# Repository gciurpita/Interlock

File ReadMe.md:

### RR Interlock - Bill Lupoli's New Haven

Arduino interlock route controller,
aligns multiple turnouts through interlock
by pressing buttons at either end of route.

Controller uses hardware shown at right.
~12V input top left to ~6V down converter to Arduino UNO board bottom left.
Three custom Tortoise Driver and I/O PCBs
using MCP23017 I2C I/O expander
to control up to 8 tortoise switch machines using LM324 op-amps and
eight GPIOs.

<!-- -----------------------------------------------  ---------------------- -->
<h4> PCB Wire Connections </h4>

<table border=1 cellspacing=0 align=right>
 <tr> <th colspan=2> PCB 4
 <tr> <th> Sw <th> But
 <tr> <td align=center> &nbsp; <td align=center>  &nbsp;
 <tr> <td align=center> &nbsp; <td align=center>  &nbsp;
 <tr> <td align=center> &nbsp; <td align=center>  &nbsp;
 <tr> <td align=center> &nbsp; <td align=center>  &nbsp;

 <tr> <td align=center> &nbsp; <td align=center>  &nbsp;
 <tr> <td align=center> &nbsp; <td align=center>  &nbsp;
 <tr> <td align=center> &nbsp; <td align=center>  &nbsp;
 <tr> <td align=center> &nbsp; <td align=center>  &nbsp;
</table>

<table border=1 cellspacing=0 align=right>
 <tr> <th colspan=2> PCB 3
 <tr> <th> Sw <th> But
 <tr> <td align=center>  69 <td align=center>  A1
 <tr> <td align=center>  70 <td align=center>  A2
 <tr> <td align=center>  71 <td align=center>  A3
 <tr> <td align=center>  72 <td align=center>  A4
 <tr> <td align=center> &nbsp; <td align=center> B1
 <tr> <td align=center> &nbsp; <td align=center> B2
 <tr> <td align=center> &nbsp; <td align=center> B3
 <tr> <td align=center> &nbsp; <td align=center> B4
</table>

<table border=1 cellspacing=0 align=right>
 <tr> <th colspan=2> PCB 2
 <tr> <th> Sw <th> But
 <tr> <td align=center>  59 <td align=center>  C1
 <tr> <td align=center>  61 <td align=center>  C2
 <tr> <td align=center>  63 <td align=center>  C3
 <tr> <td align=center>  64 <td align=center>  C4
 <tr> <td align=center>  65 <td align=center>  C5
 <tr> <td align=center>  66 <td align=center>  C6
 <tr> <td align=center>  67 <td align=center>  C7
 <tr> <td align=center>  68 <td align=center>  C8
</table>

<table border=1 cellspacing=0 align=right>
 <tr> <th colspan=2> PCB 1
 <tr> <th> Sw <th> But
 <tr> <td align=center>  51 <td align=center>  X1
 <tr> <td align=center>  52 <td align=center>  X2
 <tr> <td align=center>  53 <td align=center>  X3
 <tr> <td align=center>  54 <td align=center>  &nbsp;

 <tr> <td align=center>  55 <td align=center>  &nbsp;
 <tr> <td align=center>  56 <td align=center>  &nbsp;
 <tr> <td align=center>  57 <td align=center>  &nbsp;
 <tr> <td align=center>  58 <td align=center>  &nbsp;
</table>

<!-- -----------------------------------------------  ---------------------- -->
<h4> Panel Description  </h4>

<i>westIntLck.cpp</i> contains tables describing the panel:
buttons, turnouts and routes.
This description requires a minimal understanding of programming
to make modifications.

<p>
Descriptions of both buttons and turnouts
includes identifying the corresponding
chip and port bit along with a label.

<p>
Buttons are described in <i>butIos []</i>.
<i>Ba1</i> is a numeric symbol uniquely identifying each button,
the <i>B</i> prefix identifies it as a button and
<i>a1</i> corresponds to the label on the panel.
The <i>0, 0, "A1"</i> identifies the input on
chip 0, port bit 0 (the first or least significant bit) and
a text string label, <i>A1</i>.
There are at most 8 bits on each chip,
some spare bits are available.

<blockquote><pre>
const PROGMEM ButIo_t butIos [] = {
    { Ba1, { 0, 0, "A1" }},
    ...
    { Bc6, { 1, 5, "C6" }},
    ...
    { Bc9, { 2, 0, "C9" }},
    { Bx1, { 2, 1, "X1" }},
    { Bx2, { 2, 2, "X2" }},
    ...
    { B_0, { 0, 0, ""   }},
};
</blockquote></pre>

There is an entry for each switch machine position.
<i>s02r</i> is the variable name of the entry used in the <i>routes</i> table.
The first three fields, <i>2, R, 1</i>,
include a numeric value for the switch machine,
a symbol, <i>N/R</i> identifying the position as normal/reverse and
the bit value, 0/1 for that position.
The last three fields,
<i>0, 1, "s02r"</i>, like the button entry
specify the chip, port bit and label.

<blockquote><pre>
// machine address and polarity
const PROGMEM SwMach_t s02n = {  2, N, 0, { 0, 1, "s02n" }};
const PROGMEM SwMach_t s02r = {  2, R, 1, { 0, 1, "s02r" }};

const PROGMEM SwMach_t s14n = { 14, N, 0, { 1, 5, "s14n" }};
const PROGMEM SwMach_t s14r = { 14, R, 1, { 1, 5, "s14r" }};

const PROGMEM SwMach_t s21n = { 21, N, 0, { 2, 4, "s21n" }};
const PROGMEM SwMach_t s21r = { 21, R, 1, { 2, 4, "s21r" }};
</blockquote></pre>

Routes are described in the routes table, <i>routes []</i>.
Each entry specifies a pair a buttons and
one or more switch machine position references (i.e. pointers).

<blockquote><pre>
const PROGMEM Route_t routes [] = {
    { Ba1, Bc1, { &s21r, &s19n, &s15r, &s14n, &s06n }},
    { Ba1, Bc2, { &s21r, &s19n, &s15n, &s10n, &s06n }},
    ...
    { Ba4, Bc4, { &s20n, &s16n, &s17n, &s11n, &s12n, &s07n, &s02r, &s01n }},
    ...
}
</blockquote></pre>

Some routes are ambiguous,
a pair of buttons can select more than one route.
<blockquote><pre>
    { Ba4, Bc3, { &s20n, &s16n, &s17n, &s11n, &s12n, &s07n, &s02r, &s01r }},
    { Ba4, Bc3, { &s20r, &s16n, &s17n, &s11n, &s12n, &s07n, &s02r, &s01r }},
</blockquote>

The code repeatedly
* monitors the button input ports
* detects that two or more buttons have been pressed
* uses <i>butIos []</i> to match the chip and port bit to button IDs
* searches the routes table for an entry with that pair of buttons, and
* sets the corresponding bits to position the switch
for each machine in the route.

<!-- -----------------------------------------------  ---------------------- -->
<hr>
<h4> Code Description </h4>

<b>setup ()</b> 
sets the serial monitor bit rate,
configures pins 5-13 as outputs,
initializes the I2C interface (i.e. <i>Wire</i>) and
calls <i>i2cCfg ()</i> to configure the
I/O expanders on each switch machine driver board.

<p>
<b>loop ()</b> invokes
<ul>
 <li> <i>ledStrobe ()</i>
 <li> <i>butScan ()</i>
 <li> <i>pcRead ()</i>
 <li> <i>tglTest ()</i>
</ul>

<p>
<b>ledStrobe (void)</b>
flashes/winks an LED at one of three different sequences,
on/off periods.

<p>
<b>butScan (void)</b>
reads GPIO-B, the button input port of each chip,
checks for a change in state,
waits WAIT_CNT iterations to debounce
before recognizing that one or more buttons have been pressed and 
calling <i>mapButtons ()</i> 

<p>
<b>mapButtons ()</b>
translates the chip and port bit of the button
into a button ID (e.g. <i>Ba1</i>) using <i>butFind ()</i>,
appending the button ID to <i>list []</i> 
<i>chkRoutes ()</i> is invoked
if two or more buttons are pressed.
<i>tglTestEn</i> is toggled
if the three: <i>Ba1, Ba3</i> and <i>Ba0</i> are pressed.

<p>
<b>butFind ()</b>
searches <i>butIos []</i> for
entries matching the chip and port bit arguments.
The following <i>butIos []</i> entry
specifies a button-ID, chip, port-bit and label
<blockquote>
    { Ba1, { 0, 0, "A1" }},
</blockquote>

<p>
<b>int chkRoutes ()</b> 
searches for a route entry with matching buttons.
The following <i>routes []</i> entry
specifies two buttons followed by one or more 
pointers (e.g. <i>&amp;s21n</i> to <i>SwMach_t</i>)
<blockquote>
    { Ba1, Bc1, { &s21r, &s19n, &s15r, &s14n, &s06n }},
</blockquote>
<i>chkButtons ()</i> is used to compare the button entries from a route
to the buttons in <i>list []</i> from <i>mapButtons ()</i>.

<p>
A <i>SwMach_t</i> entry specifies
a switch machine ID, position (i.e. N/R),
bit value for that position and <i>I2cBitDef_t</i> 
which specified a chip, port bit and label
<blockquote>
const PROGMEM SwMach_t s21r = { 21, R, 1, { 2, 4, "s21r" }};
</blockquote>

<p>
<b>int chkButtons ()</b>
compares each of three possible button arguments
to each entry in <i>list []</i>.

<p>
<b>void bitUpdate ()</b> 
updates a specific port bit on a specified chip
by reading and masking the port value 
to only update the state (0, 1) of the specified bit.

<p>
<b>i2cCfg () </b> 
configures GPIO-A and B direction registers
for output and input respectively.
It enables the pull-up resistors on GPIO-B.
set GPIO-B

<p>
<b>i2cWrite (int chip, int port, byte val) </b> 
writes the 8-bit value to the specific chip and port.
After writing the direction registers
it attempts to read them back and
discontinue the loop assuming not chip exists at that bus address.

<p>
<b>i2cWrite (int chip, int port, byte val) </b> 
writes the 8-bit value to the specific chip and port.

<p>
<b>test ()</b>
sequentially sets each port bit for 500 msec
first for GPIO-A and then GPIO-B (should have no effect).

<p>
<b>tglTest (void)</b>,
when enabled,
toggles all 8-its of GPIO-A on each chip every 4 seconds.
It first tests if <i>tglTestEn</i> is set.
It then tests if the time has expired.
It then inverts <i>tglTestState</i> and
writes it to GPIO-A of each chip.

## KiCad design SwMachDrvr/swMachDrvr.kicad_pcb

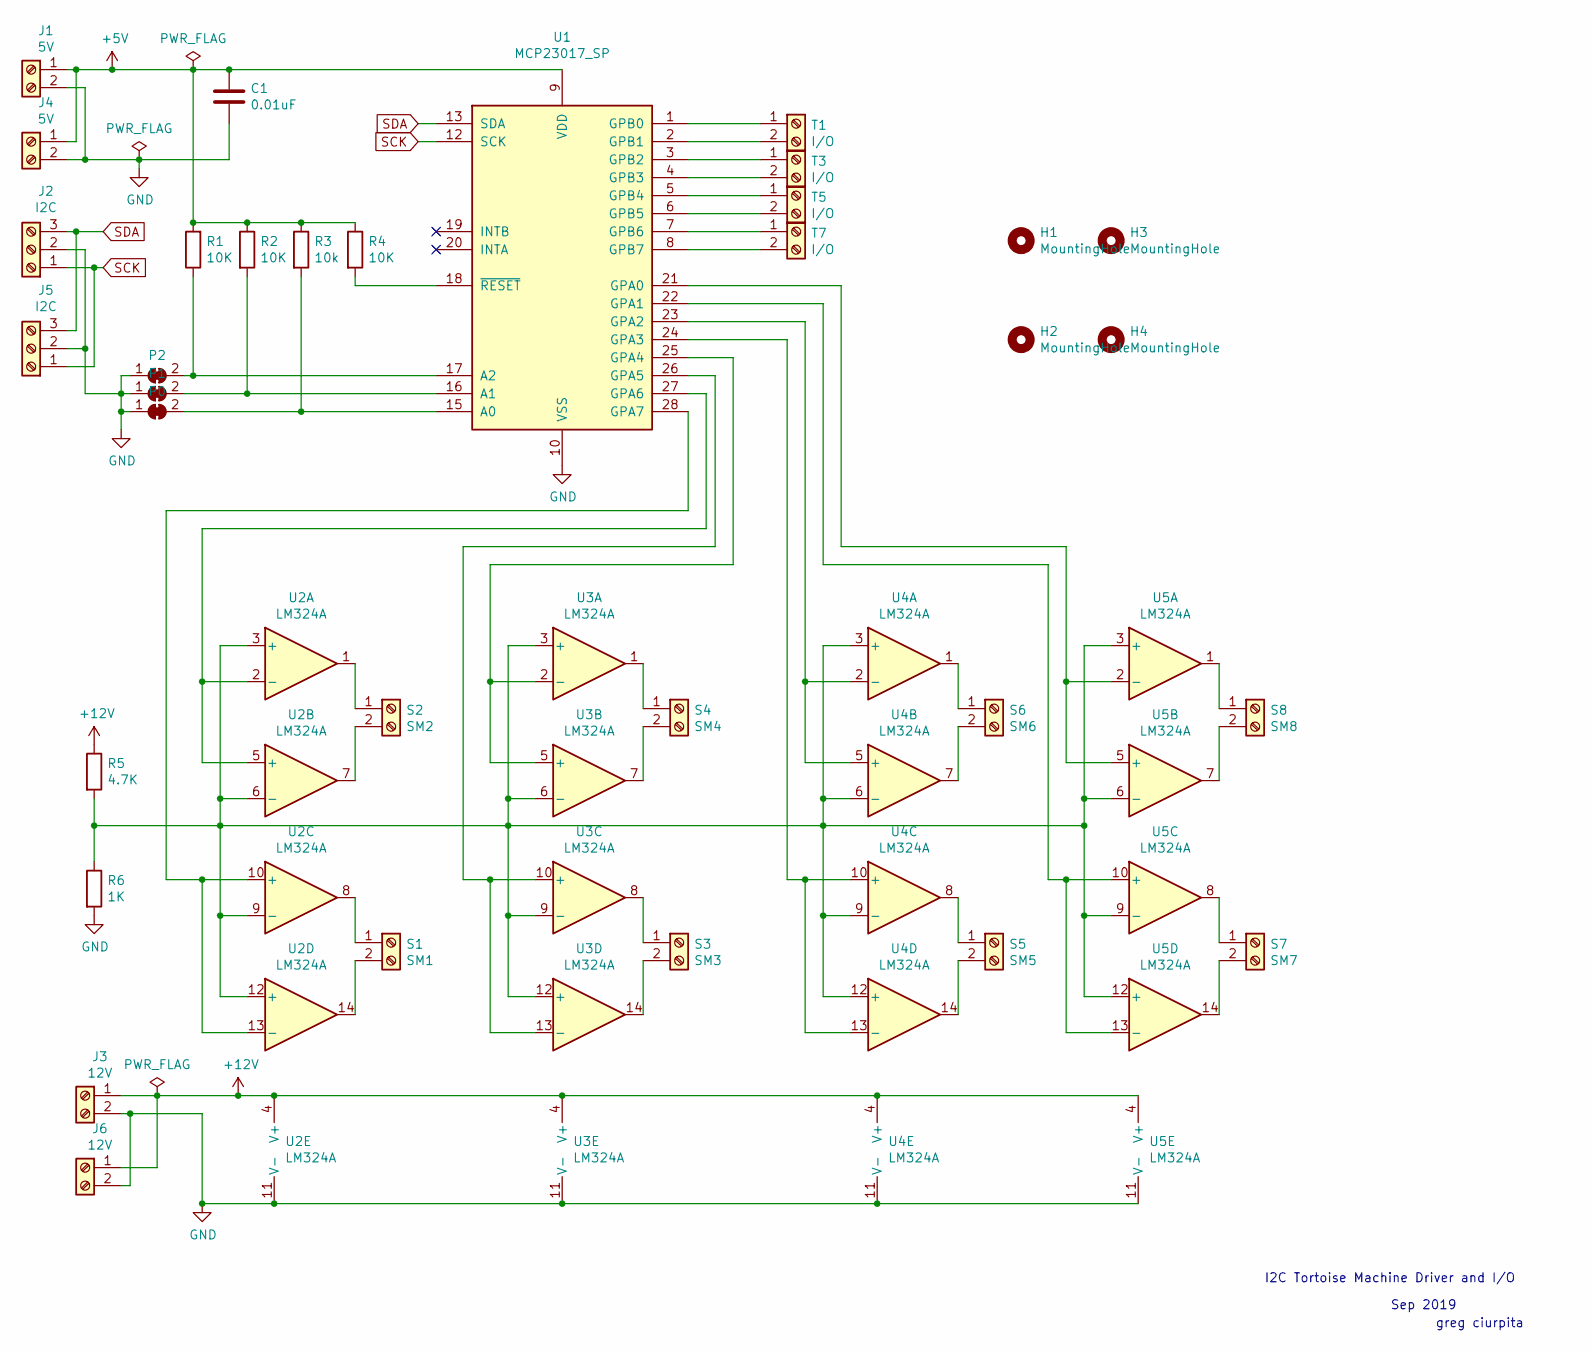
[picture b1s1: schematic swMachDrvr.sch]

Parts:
C1: 0.01uF; C_Disc_D4.3mm_W1.9mm_P5.00mm
H1, H2, H3, H4: MountingHole; MountingHole_3.5mm
J1, J4: 5V; PinHeader_1x02_P2.54mm_Vertical
J2, J5: I2C; PinHeader_1x03_P2.54mm_Vertical
J3, J6: 12V; PinHeader_1x02_P2.54mm_Vertical
P0, P1, P2: br; SolderJumper-2_P1.3mm_Bridged_RoundedPad1.0x1.5mm
R1, R2, R4: 10K; R_Axial_DIN0207_L6.3mm_D2.5mm_P7.62mm_Horizontal
R3: 10k; R_Axial_DIN0207_L6.3mm_D2.5mm_P7.62mm_Horizontal
R5: 4.7K; R_Axial_DIN0207_L6.3mm_D2.5mm_P7.62mm_Horizontal
R6: 1K; R_Axial_DIN0207_L6.3mm_D2.5mm_P7.62mm_Horizontal
S1: SM1; PinHeader_1x02_P2.54mm_Vertical
S2: SM2; PinHeader_1x02_P2.54mm_Vertical
S3: SM3; PinHeader_1x02_P2.54mm_Vertical
S4: SM4; PinHeader_1x02_P2.54mm_Vertical
S5: SM5; PinHeader_1x02_P2.54mm_Vertical
S6: SM6; PinHeader_1x02_P2.54mm_Vertical
S7: SM7; PinHeader_1x02_P2.54mm_Vertical
S8: SM8; PinHeader_1x02_P2.54mm_Vertical
T1, T3, T5, T7: I/O; PinHeader_1x02_P2.54mm_Vertical
U1: MCP23017_SP; DIP-28_W7.62mm_Socket
U2, U3, U4, U5: LM324A; DIP-14_W7.62mm_Socket

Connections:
+5V: C1.1, J1.1, J4.1, R1.2, R2.1, R3.1, R4.1, U1.9 (VDD)
+12V: J3.1, J6.1, R5.1, U2.4 (V+), U3.4 (V+), U4.4 (V+), U5.4 (V+)
GND: C1.2, J1.2, J2.2, J3.2, J4.2, J5.2, J6.2, P0.1 (A), P1.1 (A), P2.1 (A), R6.2, U1.10 (VSS), U2.11 (V-), U3.11 (V-), U4.11 (V-), U5.11 (V-)
unnamed: P0.2 (B), R3.2, U1.15 (A0)
unnamed: P1.2 (B), R2.2, U1.16 (A1)
unnamed: P2.2 (B), R1.1, U1.17 (A2)
unnamed: R4.2, U1.18 (~RESET~)
unnamed: R5.2, R6.1, U2.3 (+), U2.6 (-), U2.9 (-), U2.12 (+), U3.3 (+), U3.6 (-), U3.9 (-), U3.12 (+), U4.3 (+), U4.6 (-), U4.9 (-), U4.12 (+), U5.3 (+), U5.6 (-), U5.9 (-), U5.12 (+)
unnamed: S1.1, U2.8
unnamed: S1.2, U2.14
unnamed: S2.1, U2.1
unnamed: S2.2, U2.7
unnamed: S3.1, U3.8
unnamed: S3.2, U3.14
unnamed: S4.1, U3.1
unnamed: S4.2, U3.7
unnamed: S5.1, U4.8
unnamed: S5.2, U4.14
unnamed: S6.1, U4.1
unnamed: S6.2, U4.7
unnamed: S7.1, U5.8
unnamed: S7.2, U5.14
unnamed: S8.1, U5.1
unnamed: S8.2, U5.7
unnamed: T1.1, U1.1 (GPB0)
unnamed: T1.2, U1.2 (GPB1)
unnamed: T3.1, U1.3 (GPB2)
unnamed: T3.2, U1.4 (GPB3)
unnamed: T5.1, U1.5 (GPB4)
unnamed: T5.2, U1.6 (GPB5)
unnamed: T7.1, U1.7 (GPB6)
unnamed: T7.2, U1.8 (GPB7)
unnamed: U1.21 (GPA0), U5.2 (-), U5.5 (+)
unnamed: U1.22 (GPA1), U5.10 (+), U5.13 (-)
unnamed: U1.23 (GPA2), U4.2 (-), U4.5 (+)
unnamed: U1.24 (GPA3), U4.10 (+), U4.13 (-)
unnamed: U1.25 (GPA4), U3.2 (-), U3.5 (+)
unnamed: U1.26 (GPA5), U3.10 (+), U3.13 (-)
unnamed: U1.27 (GPA6), U2.2 (-), U2.5 (+)
unnamed: U1.28 (GPA7), U2.10 (+), U2.13 (-)
SCK: J2.1, J5.1, U1.12 (SCK)
SDA: J2.3, J5.3, U1.13 (SDA)

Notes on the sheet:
I2C Tortoise Machine Driver and I/O
Sep 2019
greg ciurpita

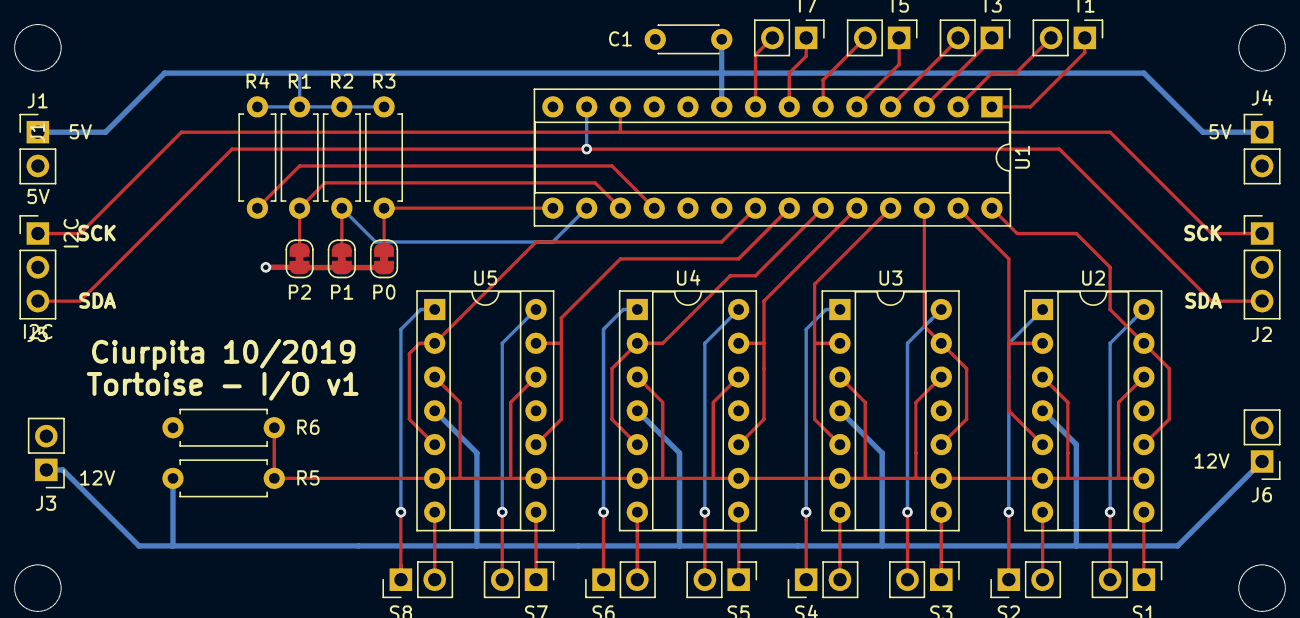
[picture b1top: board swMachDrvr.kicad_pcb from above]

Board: 2 copper layers, 37 parts (0 on the bottom side), 42 nets.

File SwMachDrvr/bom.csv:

"Id";"Designator";"Package";"Quantity";"Designation";"Supplier and ref";
1;"J6,J3";"PinHeader_1x02_P2.54mm_Vertical";2;"12V";;;
2;"S1";"PinHeader_1x02_P2.54mm_Vertical";1;"SM1";;;
3;"J4,J1";"PinHeader_1x02_P2.54mm_Vertical";2;"5V";;;
4;"J5,J2";"PinHeader_1x03_P2.54mm_Vertical";2;"I2C";;;
5;"P2,P1,P0";"SolderJumper-2_P1.3mm_Bridged_RoundedPad1.0x1.5mm";3;"br";;;
6;"C1";"C_Disc_D4.3mm_W1.9mm_P5.00mm";1;"0.01uF";;;
7;"H1,H2,H3,H4";"MountingHole_3.5mm";4;"MountingHole";;;
8;"R1,R2,R4";"R_Axial_DIN0207_L6.3mm_D2.5mm_P7.62mm_Horizontal";3;"10K";;;
9;"R3";"R_Axial_DIN0207_L6.3mm_D2.5mm_P7.62mm_Horizontal";1;"10k";;;
10;"R5";"R_Axial_DIN0207_L6.3mm_D2.5mm_P7.62mm_Horizontal";1;"4.7K";;;
11;"R6";"R_Axial_DIN0207_L6.3mm_D2.5mm_P7.62mm_Horizontal";1;"1K";;;
12;"U1";"DIP-28_W7.62mm_Socket";1;"MCP23017_SP";;;
13;"U2,U3,U4,U5";"DIP-14_W7.62mm_Socket";4;"LM324A";;;
14;"T1,T3,T5,T7";"PinHeader_1x02_P2.54mm_Vertical";4;"I/O";;;
15;"S2";"PinHeader_1x02_P2.54mm_Vertical";1;"SM2";;;
16;"S3";"PinHeader_1x02_P2.54mm_Vertical";1;"SM3";;;
17;"S4";"PinHeader_1x02_P2.54mm_Vertical";1;"SM4";;;
18;"S5";"PinHeader_1x02_P2.54mm_Vertical";1;"SM5";;;
19;"S6";"PinHeader_1x02_P2.54mm_Vertical";1;"SM6";;;
20;"S7";"PinHeader_1x02_P2.54mm_Vertical";1;"SM7";;;
21;"S8";"PinHeader_1x02_P2.54mm_Vertical";1;"SM8";;;

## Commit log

2021-05-13 original
2021-05-13 simulation
2021-05-13 added ReadMe.md
2021-05-16 KiCad files
2021-07-03 added menu detail
2021-07-09 added code descriptions
2021-07-10 corrected butScan case
2021-07-11 added description of tables in westIntLck.cpp
2021-07-11 added wiring table
2021-07-14 renumbered turnouts
2021-07-14 bill's diagram with additional trackage
2021-07-14 edited text
2021-07-16 updated diagram, combined turnouts & separate wiring tables
2021-07-16 removed suggest button D1 from diagram
2021-07-16 rewrote introduction describing board
2021-07-17 updated IDs and routes
2021-07-24 added Interlock/ and Bin/ to better org
2021-07-24 corrected Bb0 and added swListNorm/Rev
2021-07-24 correct sw IDs
2021-07-24 added button 'a' and 'b' cmds and break chkRoutes() when found
2021-08-10 reversed chips used by buttons
2021-08-10 added bitTgl(), swTurnout() and ##s cmd
2021-08-10 added i2cList(), use F() to reduce ram, indent multiple msgs
2021-08-11 added break to butScan
2021-08-11 reordered button inputs
2021-08-11 button numbering
2021-08-23 test
2021-08-23 update routes sw66 and sw56
2021-08-23 narrows PCB sw/button table
2021-08-24 route corrections
2021-09-01 route correction - use sw#56
2021-09-09 moved buttons to correct PCBs and added 4th PCB (spare)
2021-09-09 added B_N and renumbered Bxs starting at 40
2021-09-09 added one button Bx1 route
2021-09-09 added SIM cases to test one-button toggle
2021-09-21 correct x1/x2
2021-09-28 coach yard changes
2021-10-12 switch 61 fixes
